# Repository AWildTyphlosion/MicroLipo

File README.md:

# USB C Micro Lipo

Ignore this, I suck at life...

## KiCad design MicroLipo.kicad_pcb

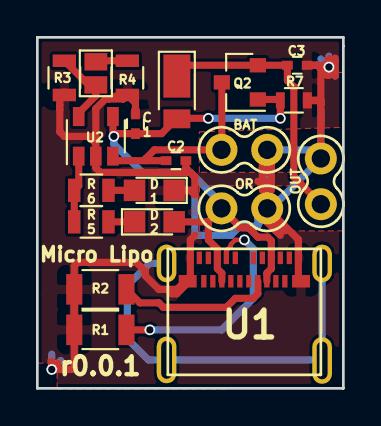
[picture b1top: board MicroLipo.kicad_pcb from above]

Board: 2 copper layers, 17.0 x 19.5 mm, 20 parts (0 on the bottom side), 11 nets.

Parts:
C1, C2: 4.7 uF; C_0402
C3: 1 uF; C_0402
D1: Green LED; LED_0805
D2: Red LED; LED_0805
D3: D_Schottky; D_PowerDI-123
J2: GS2
Q2: BSS84; SOT-23
R1, R2: 5.1K; R_1206
R3: 10K; R_0805
R4: 2.5K; R_0805
R5, R6: 470; R_0805
R7: 100K; R_0603
U1: USB-C_Molex_105450-0101; USB-C_Molex-105450-0101
U2: MCP73831/2; SOT-23-5
U3, U4, U5: 1x2; PadMount

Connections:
GND: C1.2, C2.2, C3.2, D2.1, R1.1, R2.1, R3.1, R4.1, R7.2, U1.A1, U1.A12, U1.B1, U1.B12, U2.2, U3.2, U4.2, U5.2
unnamed: C3.1, D3.1, Q2.2, U4.1
unnamed: D1.1, R5.2
unnamed: D2.2, R6.2
unnamed: J2.1, R3.2, U2.5
unnamed: J2.2, R4.2
unnamed: R1.2, U1.A5
unnamed: R2.2, U1.B5
unnamed: R5.1, R6.1, U2.1
VBUS: C1.1, D1.2, D3.2, Q2.1, R7.1, U1.A4, U1.A9, U1.B4, U1.B9, U2.4, U3.1
VC1: C2.1, Q2.3, U2.3, U5.1

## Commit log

2018-03-22 Draft Upload
2018-03-22 Added Readme
